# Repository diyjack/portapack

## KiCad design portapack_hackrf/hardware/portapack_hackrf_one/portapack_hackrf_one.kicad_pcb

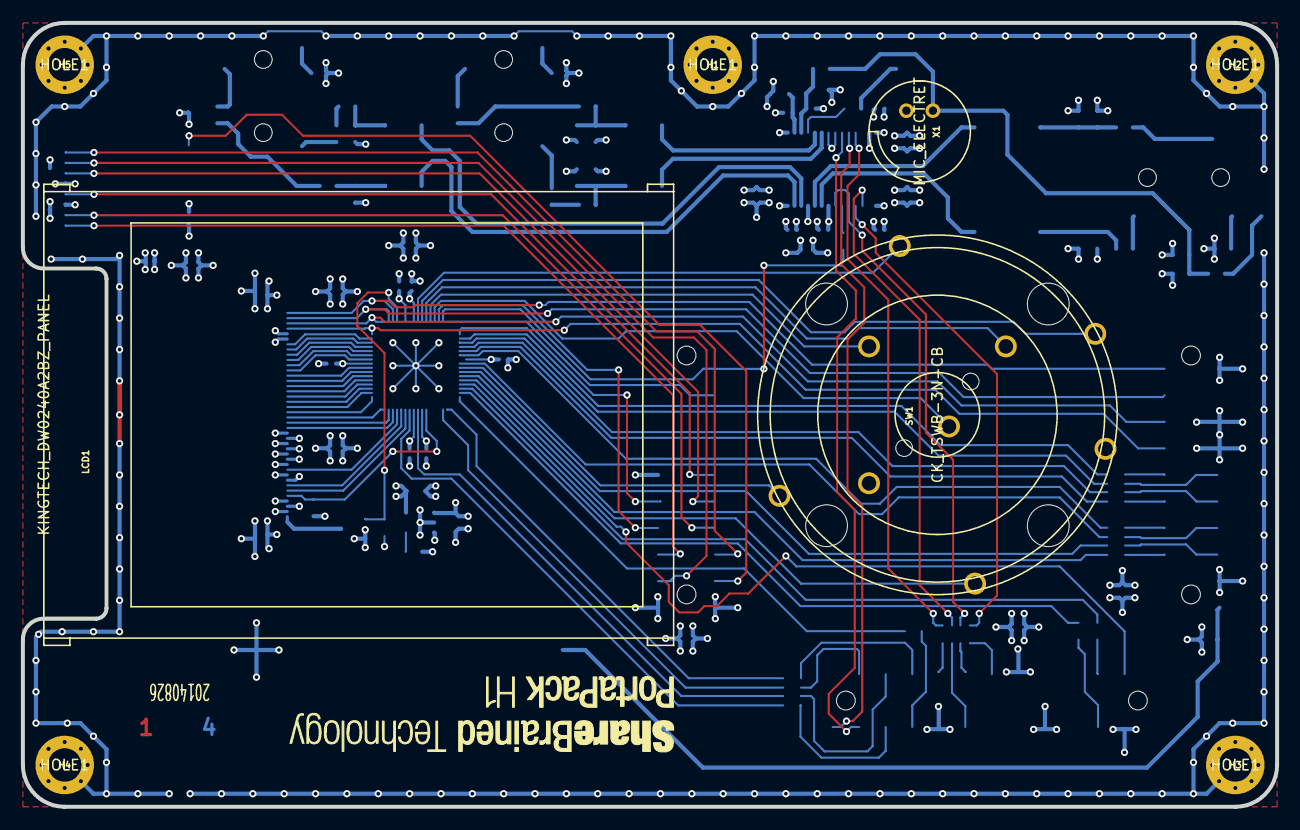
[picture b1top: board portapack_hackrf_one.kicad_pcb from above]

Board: 4 copper layers, 120.0 x 75.0 mm, 102 parts (0 on the bottom side), 123 nets.

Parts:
BT1: BATTERY; MPD_BU2032SM-BT-G
C2, C3, C4, C5, C6, C10, C27, C28, C29, C30, C31, C33, C35: 100N; IPC_CAPC1005X55N
C7, C8, C9, C11, C12, C13, C26, C32, C34, C36, C37, C38, C40, C41, C42, C43: 10U; IPC_CAPC2012X140N
C14, C15, C22, C23, C25: 220P; IPC_CAPC1608X95N
C16, C17, C24: 1U; IPC_CAPAE430X540N
C18, C19: 220U; IPC_CAPAE830X620N
C20, C21: 10U; IPC_CAPAE430X540N
C39: DNI; IPC_CAPC1608X90N
FID1, FID2, FID3, FID4: FIDUCIAL; FIDUCIAL_65MIL
H1, H2, H3, H4, H5: HOLE1; HOLE_3200UM_VIAS
J2: MICROSD_DETSW; ALPS_SCHA4B0100
J3: KINGTECH_DW0240A2BZ_FPC; MOLEX_54132-40XX_LR
L1, L2, L3, L4, L5, L6, L7, L8, L9, L10: L; IPC_INDC1608X95N
LCD1: KINGTECH_DW0240A2BZ_PANEL
LOGO1: SHAREBRAINED; sharebrained_text_300
LOGO2: PORTAPACK_H1; portapack_text_300
P1, P3: TRS_JACK; CUI_SJ-3524-SMT
P2: TRRS_SW_JACK; CUI_SJ-43516-SMT
P20: HACKRF_ONE_P20; HEADER_11X2_REV_SM_254_AP
P22: HACKRF_ONE_P22; HEADER_13X2_REV_SM_254_AP
P28: HACKRF_ONE_P28; HEADER_11X2_REV_SM_254_AP
Q1: MOSFET_N; IPC_SOT95P230X110-3N
R1, R2, R3, R22: 220R; IPC_RESC1608X55N
R6, R7, R8, R9: 5K6; IPC_RESC1608X55N
R10, R11, R12, R13, R14, R17, R19, R20: 47K; IPC_RESC1608X55N
R15, R16: 100R; IPC_RESC1608X55N
R18: 680R; IPC_RESC1608X55N
RP1, RP4, RP6, RP7: 220R; IPC_RESCAXS80P160X320X60-8N
SW1: CK_TSWB-3N-CB; CK_TSWB-3N-CB222_LFS
U1: WM8731SEDS; IPC_SOP65P780X200-28N
U2: REGULATOR_SOT23_5; IPC_SOT95P280X110-5N
U3: 5M40ZE64; IPC_QFP40P900X900X120-65N
X1: MIC_ELECTRET; CUI_CMA-4544PF-W

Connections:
+1.8V: C29.1, C31.1, C33.1, C35.1, C36.1, C37.1, C40.1, J3.36, U2.5, U3.8, U3.39, U3.41, U3.57
+3.3V: C2.1, C3.1, C4.1, C5.1, C7.1, C9.1, C11.1, C13.1, C26.1, C27.1, C28.1, C30.1, C32.1, C34.1, C38.1, C42.1, C43.1, J2.4, J3.2, J3.4, P20.3, P22.11, P28.1, U1.1, U1.8, U1.14, U1.27, U2.1, U2.3, U3.6, U3.23
/audio/I2S0_MCLK: P22.17, RP1.4
/audio/I2S0_MCLK_R: RP1.5, U1.25
/audio/I2S0_RX_SDA: R22.2, U1.6
/audio/I2S0_SCK: P22.16, RP1.3
/audio/I2S0_SCK_R: RP1.6, U1.3
/audio/I2S0_TX_SDA: P22.13, RP1.1
/audio/I2S0_TX_SDA_R: RP1.8, U1.4
/audio/I2S0_WS: P22.15, RP1.2
/audio/I2S0_WS_R: RP1.7, U1.5, U1.7
/audio/LHPOUT: C18.1, U1.9
/audio/LLINEIN: C16.1, U1.20
/audio/LOUT: C20.1, U1.12
/audio/MICBIAS: C10.1, C12.1, R18.1, U1.17
/audio/MICIN: R10.2, U1.18
/audio/RHPOUT: C19.1, U1.10
/audio/RLINEIN: C17.1, U1.19
/audio/ROUT: C21.1, U1.13
/audio/SCL: P22.26, U1.24
/audio/SDA: P22.24, U1.23
/audio/VMID: C6.1, C8.1, U1.16
/hackrf_if/CPLD_TCK: P28.17, U3.16
/hackrf_if/CPLD_TDI: P28.19, R22.1, U3.15
/hackrf_if/GPIO3_8: P20.5, RP7.3
/hackrf_if/GPIO3_8_R: RP7.6, U3.26
/hackrf_if/GPIO3_9: P20.6, RP7.4
/hackrf_if/GPIO3_9_R: RP7.5, U3.27
/hackrf_if/GPIO3_10: P20.7, RP7.2
/hackrf_if/GPIO3_10_R: RP7.7, U3.24
/hackrf_if/GPIO3_11: P20.8, RP7.1
/hackrf_if/GPIO3_11_R: RP7.8, U3.22
/hackrf_if/GPIO3_12: P20.9, RP6.3
/hackrf_if/GPIO3_12_R: RP6.6, U3.20
/hackrf_if/GPIO3_13: P20.10, RP6.4
/hackrf_if/GPIO3_13_R: RP6.5, U3.21
/hackrf_if/GPIO3_14: P20.11, RP6.2
/hackrf_if/GPIO3_14_R: RP6.7, U3.19
/hackrf_if/GPIO3_15: P20.12, RP6.1
/hackrf_if/GPIO3_15_R: RP6.8, U3.18
/hackrf_if/LCD_BACKLIGHT: Q1.1, R20.2, U3.4
/hackrf_if/LCD_DB0: J3.33, U3.62
/hackrf_if/LCD_DB1: J3.32, U3.61
/hackrf_if/LCD_DB2: J3.31, U3.60
/hackrf_if/LCD_DB3: J3.30, U3.59
/hackrf_if/LCD_DB4: J3.29, U3.58
/hackrf_if/LCD_DB5: J3.28, U3.56
/hackrf_if/LCD_DB6: J3.27, U3.55
/hackrf_if/LCD_DB7: J3.26, U3.54
/hackrf_if/LCD_DB8: J3.25, U3.53
/hackrf_if/LCD_DB9: J3.24, U3.52
/hackrf_if/LCD_DB10: J3.23, U3.51
/hackrf_if/LCD_DB11: J3.22, U3.50
/hackrf_if/LCD_DB12: J3.21, U3.49
/hackrf_if/LCD_DB13: J3.20, U3.48
/hackrf_if/LCD_DB14: J3.19, U3.47
/hackrf_if/LCD_DB15: J3.18, U3.46
/hackrf_if/LCD_RD#: J3.7, U3.44
/hackrf_if/LCD_RESET#: J3.5, R19.1, U3.38
/hackrf_if/LCD_RS: J3.6, U3.43
/hackrf_if/LCD_TE: J3.34, U3.63
/hackrf_if/LCD_WR#: J3.10, U3.45
/hackrf_if/P1_5: P28.10, U3.17
/hackrf_if/P1_8: P28.8, U3.14
/hackrf_if/P2_0: P22.20, R3.2
/hackrf_if/P2_0_R: R3.1, U3.32
/hackrf_if/P2_1: P22.19, RP4.1
/hackrf_if/P2_1_R: RP4.8, U3.33
/hackrf_if/P2_3: P22.6, R2.2
/hackrf_if/P2_3_R: R2.1, U3.31
/hackrf_if/P2_4: P22.5, R1.2
/hackrf_if/P2_4_R: R1.1, U3.30
/hackrf_if/P2_8: P22.23, RP4.2
/hackrf_if/P2_8_R: RP4.7, U3.34
/hackrf_if/P2_9: P22.21, RP4.3
/hackrf_if/P2_9_R: RP4.6, U3.40
/hackrf_if/P2_13: P22.22, RP4.4
/hackrf_if/P2_13_R: RP4.5, U3.42
/hackrf_if/RESET#: P22.3, U3.29
/hackrf_if/SD_CD: J2.B, P28.3
/hackrf_if/SD_CLK: J2.5, P28.11
/hackrf_if/SD_CMD: J2.3, P28.9
/hackrf_if/SD_DAT0: J2.7, P28.7
/hackrf_if/SD_DAT1: J2.8, P28.6
/hackrf_if/SD_DAT2: J2.1, P28.5
/hackrf_if/SD_DAT3: J2.2, P28.4
/hackrf_if/SW_D: SW1.S2, U3.10
/hackrf_if/SW_L: SW1.S5, U3.28
/hackrf_if/SW_R: SW1.S3, U3.9
/hackrf_if/SW_ROT_A: SW1.A, U3.11
/hackrf_if/SW_ROT_B: SW1.B, U3.12
/hackrf_if/SW_SEL: SW1.S1, U3.13
/hackrf_if/SW_U: SW1.S4, U3.25
/hackrf_if/TP_D: J3.38, P20.16, U3.1
/hackrf_if/TP_L: J3.39, P20.18, U3.2
/hackrf_if/TP_R: J3.37, P20.14, U3.64
/hackrf_if/TP_U: J3.40, P20.20, U3.3
/hackrf_if/VBAT: BT1.1, C41.1, P20.1
GND: BT1.2, C2.2, C3.2, C4.2, C5.2, C6.2, C7.2, C8.2, C9.2, C10.2, C11.2, C12.2, C13.2, C14.1, C15.2, C22.1, C23.2, C25.2, C26.2, C27.2, C28.2, C29.2, C30.2, C31.2, C32.2, C33.2, C34.2, C35.2, C36.2, C37.2, C38.2, C39.2, C40.2, C41.2, C42.2, C43.2, H1.1, H2.1, H3.1, H4.1, H5.1, J2.0, J2.6, J2.A, J2.SH, J3.3, J3.8, J3.9, J3.11, J3.12, J3.13, J3.14, J3.15, J3.16, J3.17, J3.35, J3.SHLD, L1.2, L6.2, L10.2, P20.13, P20.15, P20.19, P22.4, P22.10, P22.18, P28.2, P28.12, Q1.2, R8.1, R9.2, R11.1, R12.2, R13.1, R14.2, R17.2, R19.2, R20.1, SW1.CA, SW1.CB, U1.11, U1.15, U1.21, U1.22, U1.28, U2.2, U3.65, X1.2
unnamed: C14.2, C16.2, R6.1, R8.2
unnamed: C15.1, C17.2, R7.1, R9.1
unnamed: C18.2, C22.2, L4.2, R11.2
unnamed: C19.2, C23.1, L5.2, R12.1
unnamed: C20.2, R13.2, R15.2
unnamed: C21.2, R14.1, R16.2
unnamed: C24.1, R10.1
unnamed: C24.2, C25.1, L9.2, R17.1, R18.2, X1.1
unnamed: C39.1, U2.4
unnamed: J3.1, Q1.3
unnamed: L1.1, P1.1
unnamed: L2.1, R6.2
unnamed: L2.2, P1.2
unnamed: L3.1, R7.2
unnamed: L3.2, P1.3
unnamed: L4.1, P2.2
unnamed: L5.1, P2.3
unnamed: L6.1, P2.4
unnamed: L7.1, P3.2
unnamed: L7.2, R15.1
unnamed: L8.1, P3.3
unnamed: L8.2, R16.1
unnamed: L9.1, P2.1
unnamed: L10.1, P3.1

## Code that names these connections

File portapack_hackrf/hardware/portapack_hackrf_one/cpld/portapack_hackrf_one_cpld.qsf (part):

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set_location_assignment PIN_61 -to LCD_DB[1]
set_location_assignment PIN_62 -to LCD_DB[0]
set_location_assignment PIN_44 -to LCD_RDX
set_location_assignment PIN_43 -to LCD_RS
set_location_assignment PIN_63 -to LCD_TE
set_location_assignment PIN_45 -to LCD_WRX
set_location_assignment PIN_10 -to SW_D
set_location_assignment PIN_28 -to SW_L
set_location_assignment PIN_9 -to SW_R
set_location_assignment PIN_11 -to SW_ROT_A
set_location_assignment PIN_12 -to SW_ROT_B
set_location_assignment PIN_13 -to SW_SEL
set_location_assignment PIN_25 -to SW_U
set_location_assignment PIN_1 -to TP_D
set_location_assignment PIN_2 -to TP_L
set_location_assignment PIN_64 -to TP_R
set_location_assignment PIN_3 -to TP_U
set_instance_assignment -name IO_STANDARD "3.3V SCHMITT TRIGGER INPUT" -to SW_D
set_instance_assignment -name IO_STANDARD "3.3V SCHMITT TRIGGER INPUT" -to SW_L
set_instance_assignment -name IO_STANDARD "3.3V SCHMITT TRIGGER INPUT" -to SW_R
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set_instance_assignment -name PCI_IO OFF -to MCU_STROBE
set_instance_assignment -name PCI_IO OFF -to MCU_DIR
set_global_assignment -name ALLOW_LVTTL_LVCMOS_INPUT_LEVELS_TO_OVERDRIVE_INPUT_BUFFER ON
set_location_assignment PIN_4 -to LCD_BACKLIGHT
set_instance_assignment -name IO_STANDARD "3.3-V LVCMOS" -to LCD_BACKLIGHT
set_instance_assignment -name CURRENT_STRENGTH_NEW "MINIMUM CURRENT" -to LCD_BACKLIGHT
set_instance_assignment -name SLOW_SLEW_RATE ON -to LCD_BACKLIGHT
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
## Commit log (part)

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2014-06-14 Enable HackRF One RF power at start-up.
2014-06-14 #define max() (yoinked from Linux) instead of a function.
2014-06-14 Wolfson WM8731 audio codec registers header file.
2014-06-14 Remove JAWBREAKER-conditional code, expecting to support older HackRFs with new PCB design and common code.
2014-06-14 Move WM8731 I2C address declaration.
2014-06-28 CPLD configuration for 20140512 prototype.
2014-07-01 Major revision 20140701 of PortaPack H1 PCB design for second prototype. Slight changes to signal mapping to CPLD. Added lots of signal integrity and EMC tweaks, including series resistor termination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
2014-07-04 Add part info for FFC connector.
2014-07-04 CPLD: Reduce LCD data path to 16 bits.
2014-07-04 Invert LCD_BACKLIGHT to work with high side P-channel MOSFET circuit.
2014-07-04 CPLD: Change pin mappings to match 20140701 board revision. CPLD: Change voltage levels to support 1.8V LCD interface. CPLD: Turn off PCI clamps on pins with VCCIO=1.8V but 3.3V CMOS inputs. Turn off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
2014-07-08 Updated component manufacturer/part numbers and values to reflect latest build.
2014-07-08 Remove separate CODEC_VDD, replace with 3.3V. Let KiCad rename all the power nets.
2014-07-08 Remove LCD backlight current resistor.
2014-07-15 Set microphone gain to -1.1dB with 47K resistor.
2014-07-15 Changed C&K navigation switch from black to white part number.
2014-07-17 Changed LCD backlight switch back to N-type MOSFET, changed CPLD pin.
2014-07-17 Updated schematic revision to 20140717.
2014-07-17 Update schematic PDF, netlist, component footprints, PCB from schematic changes.
2014-07-20 Extract M4 core handlers into separate .c/.h files. TODO: There's a lot of leakage from portapack.c that needs to be addressed.
2014-07-20 Extract M4 client code into separate .c/.h files. Extract common code between M4 client and server into separate .h file. Change return type on ipc_channel_read() to remove dependency on specific IPC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
2014-07-20 Hide details of IPC implementation (kfifo, raising interrupt on other core) behind new ipc_channel_write() function.
2014-07-20 Rename UI function to avoid name collision with soon-to-be-renamed baseband function.
2014-07-20 Hide GPDMA details behind wait_for_completed_baseband_buffer().
2014-07-20 Move responsibility for tracking DSP block output sample count to individual functions which decimate.
2014-07-20 Improve comments in demodulation functions.
2014-07-21 Break out code to determine completed baseband buffer.
2014-07-21 Move audio output code to separate function, call from individual baseband processing functions that produce audio.
2014-07-21 Rework gain structure in NBFM and AM RX processing chains. Switch from right shifts (not guaranteed to be arithmetic in C for signed values) to divide-by-two operations.
2014-07-24 Console: add function to write a formatted uint32_t.
2014-07-24 LCD: Return prior color when setting new fore/background color.
2014-07-24 Console: Maintain own fore/background colors, restoring prior colors after drawing.
2014-07-24 LCD: Clean up internal use of passed-in argument.
2014-07-24 Demodulate: Add AM demodulator that returns float32 instead of uint16_t.
2014-07-24 Encoder: Move code to M0, poll instead of interrupt because interrupts were catching mechanical switch noise and causing erratic behavior. TODO: Poll with a timer instead of from LCD drawing loop.
2014-07-24 IPC: Add IPC code for M0 work queue.
2014-07-24 Baseband: Add signal processing for access code detection, clock recovery, envelope tracking, integration, and accumulating bits into packets.
2014-07-25 Envelope: HACK! Add small constant to avoid NaNs.
2014-07-25 Change type of packet data to bytes, kill endianness problems.
2014-07-25 Add Manchester decoder, use when decoding packet data.
2014-07-25 Integrator: Reduce size of array to match hard-coded scaling factor, which is ultimately a sad hack...
2014-07-25 UI: Wrap displaying of M4 CPU metrics in a #define so I can switch it on easily. Still ugly...
2014-07-25 RX TPMS: Initial OOK implementation.
    TODO: Some hard-coded demodulation bits still.
    TODO: Remove I2S dependency.
2014-07-26 RX TPMS: Altered packet structure for example TPMS signal to match FCC information.
2014-07-26 RX TPMS: Removed symbol integrator/filter
    Filter was too narrow and failing to pick up transmissions where there was a significant (but reasonable) carrier offset.
2014-07-27 Decimate: Correct scaling
    Scaling of a couple of real decimators relied on right shifts -- behavior is unpredictable in C99. Fix by doing proper power-of-two divide.
2014-07-29 Decimate: Make fir_64_decim_2_real_s16_s16 more generic.
2014-07-29 LCD: Add red color constant.
2014-07-29 TPMS: Add basic FSK demodulator and decoder.
2014-07-29 TPMS: Rename ASK code/files.
2014-07-29 UI: Adjust display names of different demodulation modes.
2014-07-29 Expose copy_to_audio_output() for use in various demodulators.
2014-07-29 Extract FM broadcast demodulator into separate files.
2014-07-29 More demodulator refactoring.
    Moved filter taps into filters.c.
    Moved FM narrowband and AM demodulators into separate files.
2014-07-29 Remove unnecessary #include.
2014-07-29 Encoder: Move initialization from M4 to M0.
2014-07-29 Baseband: Make receiver_configuration_t private.
2014-07-29 Baseband: Remove some dead code.
2014-07-29 Baseband: Use actual sampling rate in DSP metrics.
2014-07-29 Baseband: Move SGPIO DMA ack to end of interrupt.
    This prevents locking up the baseband at 100% CPU utilization if the baseband handler does not complete in one baseband frame. Instead a baseband frame is dropped.
2014-07-29 Specan: Adapt FFT code to baseband handler interface.
2014-07-29 Baseband: Make handlers responsible for work buffers.
    Handlers now create their own work buffers on the stack.
2014-07-29 Specan: Extract into separate files.
2014-07-29 UI: Remove unused (and too small!) font.
2014-07-30 Baseband: Enlarge baseband handler structure buffer size.
2014-07-30 UI: Remove some dead code.
2014-07-30 Specan, IPC: Handing spectrum data between cores.
2014-07-30 More dead code removal.
2014-07-30 RTC: Test if 32.768kHz oscillator is running, init and wait if not.
2014-07-30 PCB: PortaPack H1 20140717_0930
2014-07-30 Baseband: Remove enable_spectrum flag for receiver configurations.
2014-07-31 Baseband: Remove unused "name" field from receiver_configuration_t.
2014-07-31 Specan: Improve sampling rate, decimation, filter bandwidth.
2014-07-31 LCD: Fix/HACK to correct scroll update row.
2014-07-31 TPMS: Extract console coloring code.
2014-07-31 UI: Fix dumb overflow when displaying frequencies >= 2^31.
2014-07-31 Encoder: Remove LED indicators for quadrature state.
2014-07-31 RTC: Interrupt support.
2014-07-31 UI: Add RTC interrupt to update date/time when second increments.
2014-07-31 Add RI timer API.
2014-07-31 UI: Use RI timer to create 1kHz encoder update rate.
2014-07-31 IPC: Add M0 command called when RTC second increments.
2014-07-31 UI: Use RTC command sent from interrupt to update on-screen time.
2014-08-01 ADC: Reminder to move #defines from lcd_touch code to libopencm3.
2014-08-01 RSSI: Initial implementation
2014-08-05 JTAG: Abstract PortaPack JTAG code for eventual use with HackRF CPLD.
2014-08-12 CPLD: Remove codec enable signal.
2014-08-12 CPLD: Slight syntax change.
2014-08-12 CPLD: Remove codec enable signal from pinout.
2014-08-19 PCB: Change fp-lib-table for new repo/directory name.
2014-08-19 PCB: Footprint and trace changes to add SMT header alignment pins.
    Also removed fills to keep commit/repo size down.
2014-08-19 CMake: Use variable substitution for HackRF dependencies
2014-08-20 Console: Change init argument
2014-08-20 UI: Reset console when switching receiver modes.
2014-08-20 LCD: Refactor scroll functions.
2014-08-20 Console: Reset scroll position on init.
2014-08-21 TPMS: Simplify half-band/translation filtering.
2014-08-21 TPMS: Eliminate sqrtf, floats computing filter power difference.
2014-08-21 TPMS: Add comments about dynamic range of variables.
2014-08-21 UI: Fix SDIO call return variable types.
2014-08-22 Clean up a bunch of sloppy type casting.
2014-08-22 Touch: Remove excess arguments in function calls.
2014-08-23 C++: Add extern "C" for ISR functions.
2014-08-23 C++: Remove indices specified in array initialization.
2014-08-24 Clean up uninitialized array warning.
2014-08-24 Initialize all fields of structs.
2014-08-24 Specan: Reduce bandwidth to 10MHz.
2014-08-24 FIFO: Switch to C++ implementation.
2014-08-24 C++: Rename all the files!
2014-08-24 Remove linux_stuff.h, add missing bits to portapack.h.
2014-08-24 Fix M4 command handler array indices.
2014-08-24 Fix #include for __RBIT().
2014-08-24 snprintf and strnlen aren't available, so use non-N variants.
2014-08-24 Replace array of pointers with std::vector.
2014-08-24 UI: Add ui_widget_t parent to UI class(es).
2014-08-25 UI: Push ui_widget_t deep into code, use inheritance.
2014-08-25 UI: Back off on C++ inheritance. It wasn't paying off in code size.
2014-08-25 UI: Clean up code around tuning step sizes.
2014-08-25 UI: Change from vector to array to reduce code size.
2014-08-25 UI: Remove key repeat code.
2014-08-25 UI: Convert touch keypad rendering to C++ idioms.
2014-08-25 UI: Remove some superfluous functions.
2014-08-25 Remove blink(), which might reappear in the LED API?
2014-08-25 UI: Reorder code in handle_joysticks. Better locality.
2014-08-26 PCB: Segmented CPLD paste aperture.
2014-08-26 UI: Add ui_widget_t flags to selectively disable focus behavior.
2014-08-26 UI: Rearrange fields on screen.
2014-08-26 UI: Add CPU% bar.
2014-08-26 UI: Add RSSI bar.
2014-08-30 SDIO: Use two clock speeds and function to switch.
2014-08-30 SDIO: Hacky function to convert INTSTS to sdio_error_t.
2014-08-30 SDIO: Change register field style, remove extra functions.
2014-08-30 SDIO: Change CRC/response expectations of some commands.
2014-08-30 SDIO: Change interface on ACMD41 to take HCS.
2014-08-30 SDIO: Add CMD7 function.
2014-08-30 SDIO: Add single-block read function (CMD17).
2014-08-30 SDIO: Add single-block write function (CMD24).
2014-08-30 SDIO: Make CMD55 a bit more explicit.
2014-08-30 SDIO: Enable low-power clock mode.
2014-08-30 SDIO: Expose CMD2, CMD3 functions.
2014-08-30 FATFS: Initial commit of files from release R0.10b.
2014-08-30 FATFS: Add to firmware CMake.
2014-08-30 SDIO: Change card init, perform FATFS state management.
2014-08-30 FATFS: Log TPMS packets to file.
2014-08-30 Encoder: Ditch the interrupt-based code, it worked terribly.
2014-08-31 RTC: Move PPS interrupt to M4, remove IPC M0 client from M0 binary.
2014-09-08 Decimate: Add 8:1 complex FIR filter.
2014-09-08 IPC: Enlarge M4 and M0 IPC FIFOs.
2014-09-08 TPMS: Comment about how my FSK demod works.
2014-09-08 SDIO: Remove garbage comments.
2014-09-08 RSSI: Speed up time constant to better see bursty data.
2014-09-08 RSSI: Track peak value.
2014-09-15 PCB: Hand-segment CPLD thermal pad solder paste aperture.
2014-10-11 Update schematic date to reflect final PCB design.
2014-10-11 Console: Add console_write_int32.
2014-10-11 CPLD: Add programming data file.
2014-10-11 CPLD: Unbreak programming code.
2014-10-11 UI: Remove SDIO activity indicators.
2014-10-11 SDIO: Change name of log file to be generic for now.
2014-10-11 SDIO: Change timing of FATFS card present flag after card detect.
2014-10-11 Log: Consolidate simple API for logging to SD card.
2014-10-11 Change receiver_configuration_index to size_t.
2014-10-11 Turn UI-side receiver configuration names into array, simplify formatting.
2014-10-11 UI: Guard against invalid receiver configuration ordinal.
2014-10-11 Incorporate packet data handler into array of receiver modes.
2014-10-13 Silence unused variable warnings.
2014-10-13 M0: Speed up SPIFI for flash code execution.
2014-10-13 Disable reset of all peripherals at boot, until SPIFI can be initialized from scratch.
2014-10-13 PCB: Set drill/place origin to top-left corner of PCB.
2014-10-13 Minor update to BOM, component values, DNI status in schematic.
2014-10-14 Bring HackRF project module into this project.
2014-10-14 CPLD: Change for latest PCB LCD backlight control.
2014-10-21 Add GCC fix to get rid of extra sections and slim down image.
2014-10-21 RTC: Retrieve date/time as a single call returning a structure.

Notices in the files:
portapack_hackrf/hardware/portapack_hackrf_one/cpld/portapack_hackrf_one_cpld.qsf:
Copyright (C) 1991-2014 Altera Corporation
